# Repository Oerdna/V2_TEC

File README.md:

# V2_TEC
Redesigned PCB for simultaneous Peltier control and surface resistance measurement

------

## Composition
The complex consists of two boards - Signal and Power. The power acts like as a controller of the Peltier element. Signal measures surface resistance and temperature.
In the table, the top line is the signal board. Lower - power. Drawings as part of a work of art.

|  |  |
| ------------------------------------------------------------ | ------------------------------------------------------------ |
|  |  |

More details about the device can be understood from the schematic drawing [here](https://github.com/Oerdna/V2_TEC/blob/main/TEC2/TEC2.pdf). The notes are in Russian.

The controller for the complex is `STM32L432KC Nucleo`.

## Reference Information:
* To control the Peltier element, a `100 kHz PWM` is used.
* `IRS2104` is used to control transistors.
* The measurement of surface resistance is carried out by the `four-probe method`.
* Temperature measurement is carried out by `pt100`.
* There is an additional port for the `I2C` protocol

## 4point_probe

 |  | Four point probe is used to measure resistive properties of semiconductor wafers and thin films [[1](https://www.pveducation.org/pvcdrom/characterisation/four-point-probe-resistivity-measurements)]. |
| ------------------------------------------------------------ | ------------------------------------------------------------ |

In this case are studing the I - V characteristic of an element depending on the temperature of the sample. It is important to understand the I – V characteristic near the metal-insulator phase transition (MIT), which is about 68 degrees Celsius. You must understand that the ultimate goal is to stabilize the temperature to a specific value. More about the TEC control [[2](https://www.maximintegrated.com/en/design/technical-documents/tutorials/1/1757.html)]

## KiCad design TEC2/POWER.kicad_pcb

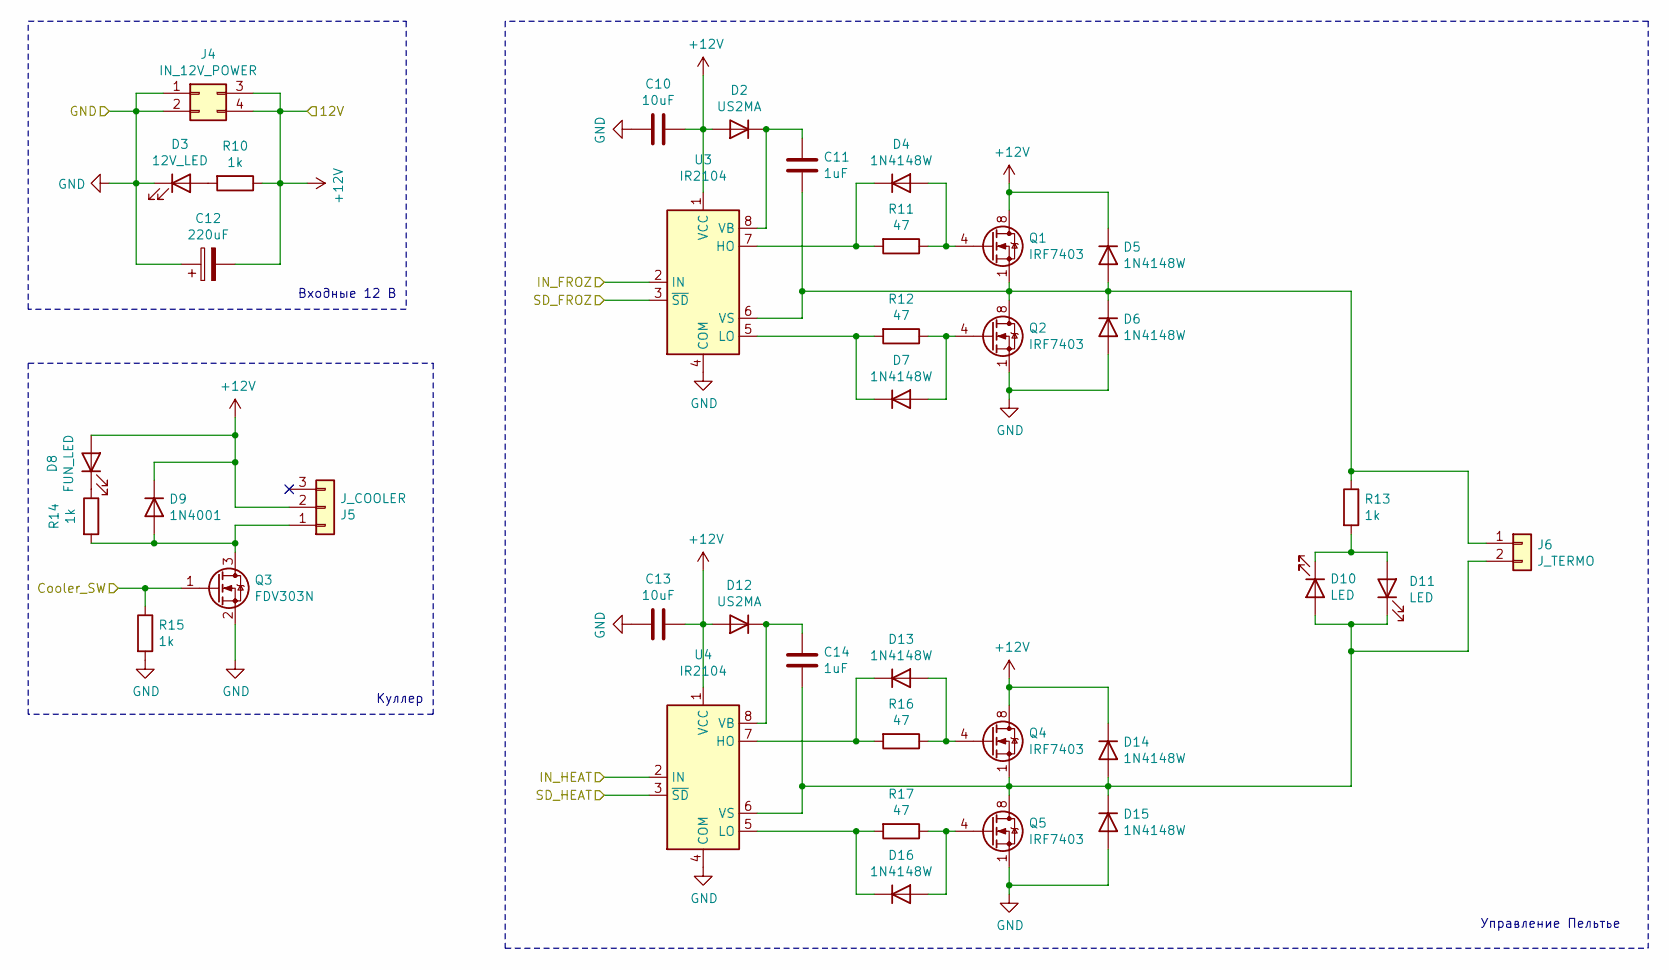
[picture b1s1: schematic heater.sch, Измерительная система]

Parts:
C10, C13: 10uF; C_0805_2012Metric_Pad1.18x1.45mm_HandSolder; JLC 0805
C11, C14: 1uF; C_0805_2012Metric_Pad1.18x1.45mm_HandSolder; JLC 0805
C12: 220uF; CP_Elec_8x10.5
D2, D12: US2MA; D_SMA
D3: 12V_LED; LED_1206_3216Metric_Castellated
D4, D5, D6, D7, D13, D14, D15, D16: 1N4148W; D_SOD-123
D8: FUN_LED; LED_1206_3216Metric_Castellated
D9: 1N4001; D_SMA-SMB_Universal_Handsoldering
D10, D11: LED; LED_0805_2012Metric_Castellated
J4: IN_12V_POWER; Molex_Mini-Fit_Jr_5569-04A2_2x02_P4.20mm_Horizontal
J5: J_COOLER; PinHeader_1x03_P2.54mm_Horizontal
J6: J_TERMO; Amass_XT60PW-M
Q1, Q2, Q4, Q5: IRF7403; SOIC-8_3.9x4.9mm_P1.27mm
Q3: FDV303N; SOT-23
R10, R13, R14, R15: 1k; R_1206_3216Metric_Pad1.30x1.75mm_HandSolder; JLC 1206
R11, R12, R16, R17: 47; R_2512_6332Metric_Pad1.40x3.35mm_HandSolder
U3, U4: IR2104; SOIC-8_3.9x4.9mm_P1.27mm

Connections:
+12V: C10.2, C12.2, C13.2, D2.2 (A), D5.1 (K), D8.2 (A), D9.1 (K), D12.2 (A), D14.1 (K), J4.3, J4.4, J5.2, Q1.5 (D), Q1.6 (D), Q1.7 (D), Q1.8 (D), Q4.5 (D), Q4.6 (D), Q4.7 (D), Q4.8 (D), R10.1, U3.1 (VCC), U4.1 (VCC); also elsewhere on the board
/IN_F: U3.2 (IN); also elsewhere on the board
/IN_H: U4.2 (IN); also elsewhere on the board
/SD_F: U3.3 (~SD); also elsewhere on the board
/SD_H: U4.3 (~SD); also elsewhere on the board
/SW_C: Q3.1 (G), R15.1; also elsewhere on the board
GND: C10.1, C12.1, C13.1, D3.1 (K), D6.2 (A), D15.2 (A), J4.1, J4.2, Q2.1 (S), Q2.2 (S), Q2.3 (S), Q3.2 (S), Q5.1 (S), Q5.2 (S), Q5.3 (S), R15.2, U3.4 (COM), U4.4 (COM); also elsewhere on the board
unnamed: C11.1, D2.1 (K), U3.8 (VB)
unnamed: C11.2, D5.2 (A), D6.1 (K), J6.1, Q1.1 (S), Q1.2 (S), Q1.3 (S), Q2.5 (D), Q2.6 (D), Q2.7 (D), Q2.8 (D), R13.1, U3.6 (VS)
unnamed: C14.1, D12.1 (K), U4.8 (VB)
unnamed: C14.2, D10.2 (A), D11.1 (K), D14.2 (A), D15.1 (K), J6.2, Q4.1 (S), Q4.2 (S), Q4.3 (S), Q5.5 (D), Q5.6 (D), Q5.7 (D), Q5.8 (D), U4.6 (VS)
unnamed: D3.2 (A), R10.2
unnamed: D4.1 (K), R11.2, U3.7 (HO)
unnamed: D4.2 (A), Q1.4 (G), R11.1
unnamed: D7.1 (K), R12.2, U3.5 (LO)
unnamed: D7.2 (A), Q2.4 (G), R12.1
unnamed: D8.1 (K), R14.1
unnamed: D9.2 (A), J5.1, Q3.3 (D), R14.2
unnamed: D10.1 (K), D11.2 (A), R13.2
unnamed: D13.1 (K), R16.2, U4.7 (HO)
unnamed: D13.2 (A), Q4.4 (G), R16.1
unnamed: D16.1 (K), R17.2, U4.5 (LO)
unnamed: D16.2 (A), Q5.4 (G), R17.1

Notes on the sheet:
Куллер
Управление Пельтье
Входные 12 В

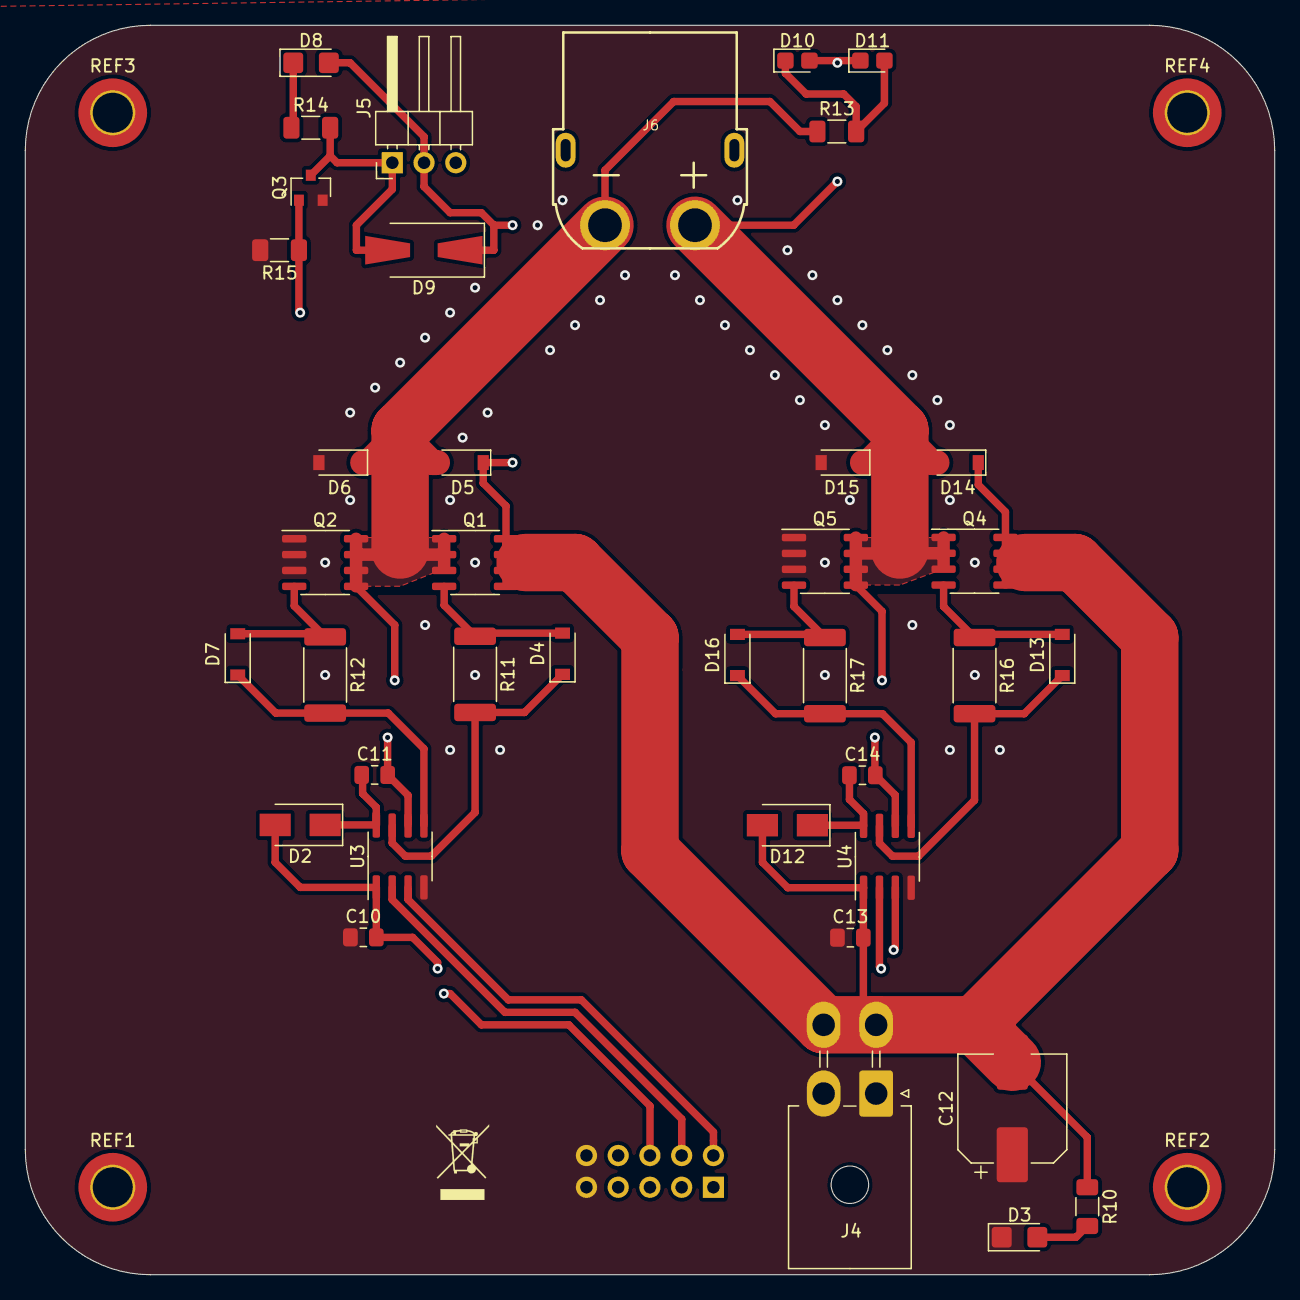
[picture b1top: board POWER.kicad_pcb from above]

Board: 4 copper layers, 100.0 x 100.0 mm, 43 parts (1 on the bottom side), 23 nets.

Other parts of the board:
J2: J_PCB_DOWN; PinHeader_2x05_P2.54mm_Vertical
REF1, REF2, REF3, REF4: MountingHole_3.2mm_M3_ISO14580_Pad_TopOnly

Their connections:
+12V: J2.7, J2.8; also elsewhere on the board
/IN_F: J2.4; also elsewhere on the board
/IN_H: J2.3; also elsewhere on the board
/SD_F: J2.2; also elsewhere on the board
/SD_H: J2.1; also elsewhere on the board
/SW_C: J2.6; also elsewhere on the board
GND: J2.9, J2.10; also elsewhere on the board

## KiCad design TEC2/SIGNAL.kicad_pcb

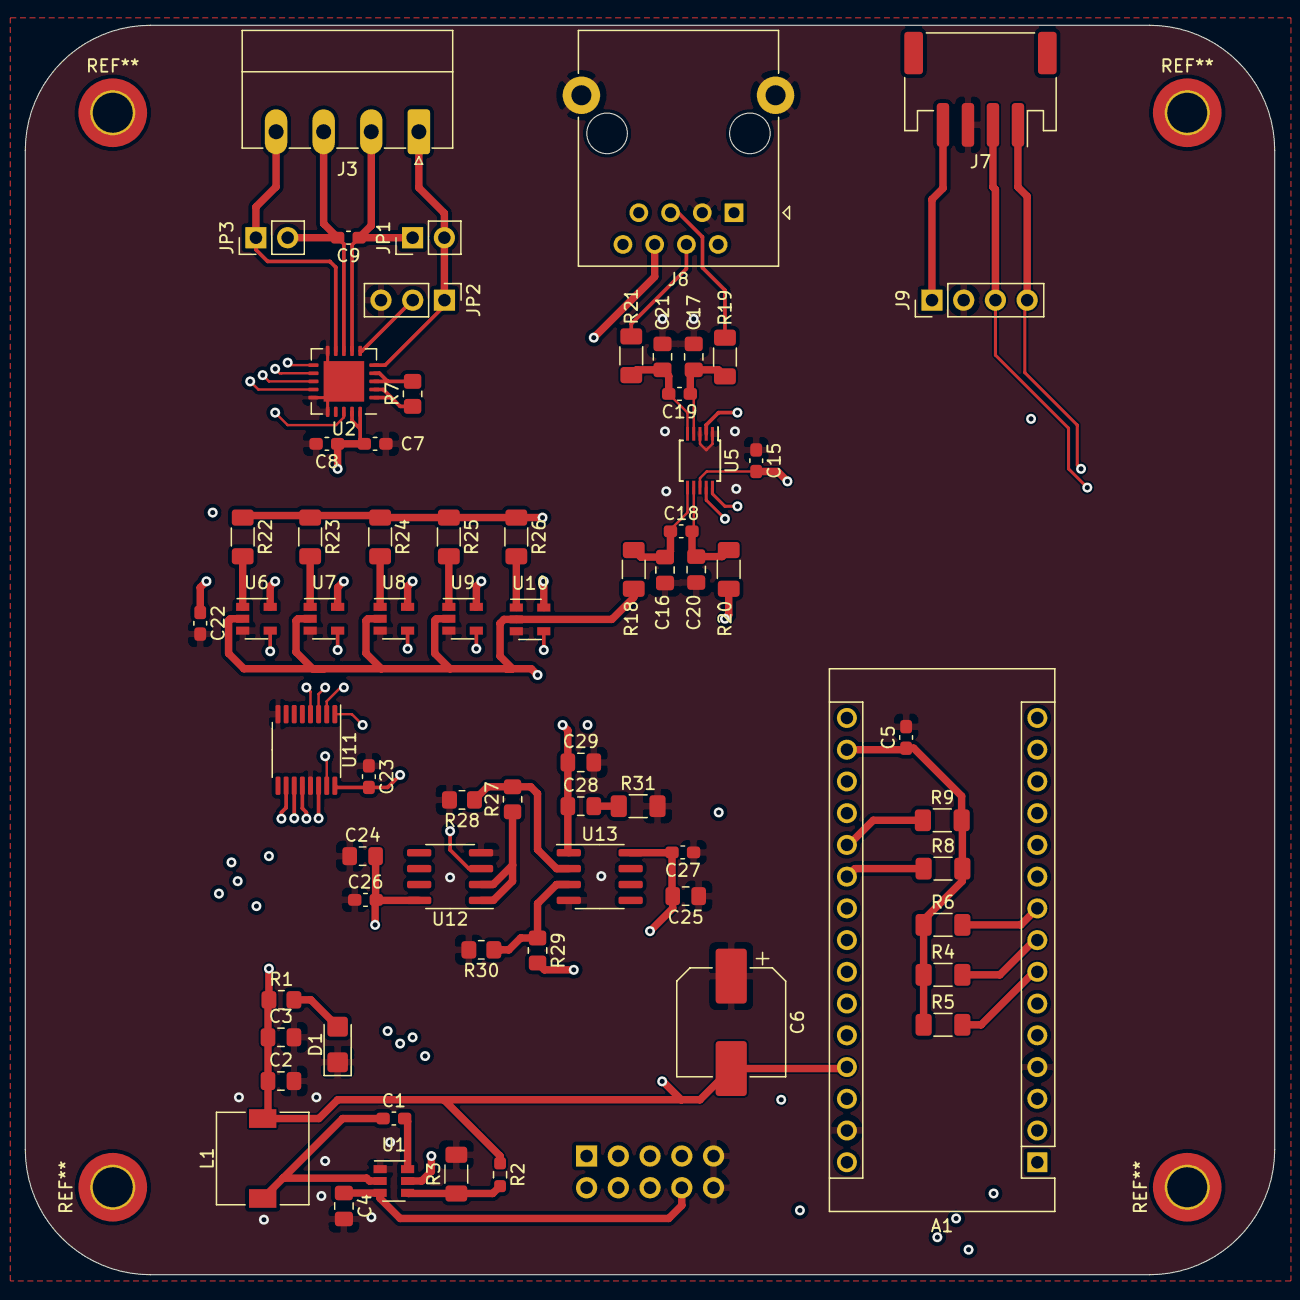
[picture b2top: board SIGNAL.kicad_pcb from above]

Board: 4 copper layers, 100.0 x 100.0 mm, 69 parts (1 on the bottom side), 55 nets.

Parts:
A1: Arduino_Nano_v3.x; Arduino_Nano
C1, C5, C7, C8, C9, C15, C22, C23, C26, C27: 100nF; C_0603_1608Metric_Pad1.08x0.95mm_HandSolder
C2, C3, C4, C24, C25: 10uF; C_0805_2012Metric_Pad1.18x1.45mm_HandSolder
C6: 220uF; CP_Elec_8x10.5
C16, C17, C20, C21, C29: 6nF; C_0805_2012Metric_Pad1.18x1.45mm_HandSolder
C18, C19: 62nF; C_0603_1608Metric_Pad1.08x0.95mm_HandSolder
C28: 470nf; C_0805_2012Metric_Pad1.18x1.45mm_HandSolder
D1: 5V_LED; LED_1206_3216Metric_Castellated
J1: J_PCB_UPPER; PinHeader_2x05_P2.54mm_Vertical
J3: ToPT100; PhoenixContact_MC_1,5_4-G-3.81_1x04_P3.81mm_Horizontal
J7: I2C_Port; JST_PH_S4B-PH-SM4-TB_1x04-1MP_P2.00mm_Horizontal
J8: RJ45_Shielded; RJ45_Ninigi_GE
J9: I2C_dbg; PinHeader_1x04_P2.54mm_Vertical
JP1: SJ2; PinHeader_1x02_P2.54mm_Vertical
JP2: SJ1; PinHeader_1x03_P2.54mm_Vertical
JP3: SJ3; PinHeader_1x02_P2.54mm_Vertical
L1: 4.7uH; L_7.3x7.3_H4.5
R1: 430; R_0805_2012Metric_Pad1.20x1.40mm_HandSolder
R2: 56.2k; R_0603_1608Metric_Pad0.98x0.95mm_HandSolder
R3, R4, R5, R6, R8, R9, R26: 10k; R_1206_3216Metric_Pad1.30x1.75mm_HandSolder
R7: 390; R_0805_2012Metric_Pad1.20x1.40mm_HandSolder
R18, R19, R20, R21, R24, R31: 100; R_1206_3216Metric_Pad1.30x1.75mm_HandSolder
R22: 1; R_1206_3216Metric_Pad1.30x1.75mm_HandSolder
R23: 10; R_1206_3216Metric_Pad1.30x1.75mm_HandSolder
R25: 1k; R_1206_3216Metric_Pad1.30x1.75mm_HandSolder
R27, R30: 20k; R_0805_2012Metric_Pad1.20x1.40mm_HandSolder
R28, R29: 13k; R_0805_2012Metric_Pad1.20x1.40mm_HandSolder
U1: TPS562200; SOT-23-6
U2: MAX31865xTP; TQFN-20-1EP_5x5mm_P0.65mm_EP3.25x3.25mm
U5: ADS1115IDGS; TSSOP-10_3x3mm_P0.5mm
U6, U7, U8, U9, U10: TS5A3166DBVR; SOT-23-5
U11: 74HC595; TSSOP-16_4.4x5mm_P0.65mm
U12: AD8572; SOIC-8_3.9x4.9mm_P1.27mm
U13: AD8606ARZ; SOIC-8_3.9x4.9mm_P1.27mm

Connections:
+3V3: A1.17, C5.1, C7.2, C8.1, C22.1, C23.2, J7.4, J9.1, R4.1, R5.1, R6.1, R8.2, R9.2, U2.19, U2.20, U6.5, U7.5, U8.5, U9.5, U10.5, U11.16
+5V: A1.27, C2.1, C3.1, C6.2, C15.2, C24.2, C25.2, C26.2, C27.2, L1.2, R1.1, R2.1, U5.8, U12.8, U13.8
+12P: C4.1, J1.7, J1.8, U1.3, U1.5
/4PP/AIN_I1: C16.2, C18.1, R18.1, U5.6
/4PP/AIN_I2: C18.2, C20.1, R20.1, U5.7
/4PP/AIN_V1: C17.2, C19.1, R19.1, U5.4
/4PP/AIN_V2: C19.2, C21.1, R21.1, U5.5
/4PP/PROBE1: J8.5, R19.2
/4PP/PROBE2: J8.4, R21.2
/4PP/R1: U6.4, U11.15
/4PP/R1k: U9.4, U11.3
/4PP/R10: U7.4, U11.1
/4PP/R10k: U10.4, U11.4
/4PP/R100: U8.4, U11.2
/4PP/R_sel_high: C28.1, C29.1, R18.2, U6.2, U7.2, U8.2, U9.2, U10.2, U13.1
/4PP/R_sel_low: J8.6, R20.2, R22.1, R23.1, R24.1, R25.1, R26.1, U12.3
/ADS1115_RDY: A1.9, R6.2, U5.2
/CLK_SPI: A1.23, U2.12
/CLK_serial: A1.2, U11.11
/Clear_serial: A1.6, U11.10
/Cooler_SW: A1.16, J1.6
/DAC_out: A1.22, R29.2
/Data_serial: A1.1, U11.14
/IN_FROZ: A1.12, J1.4
/IN_HEAT: A1.13, J1.3
/MISO: A1.24, U2.14
/MOSI: A1.25, U2.11
/SCL_i2c: A1.8, J7.1, J9.4, R4.2, U5.10
/SDA_i2c: A1.7, J7.2, J9.3, R5.2, U5.9
/SD_FROZ: A1.14, J1.2
/SD_HEAT: A1.15, J1.1
/Store_serial: A1.5, U11.12
/TEMP_CS: A1.21, R8.1, U2.13
/TEMP_RDY: A1.20, R9.1, U2.18
GNDD: A1.4, A1.29, C2.2, C3.2, C4.2, C5.2, C6.1, C7.1, C8.2, C15.1, C16.1, C17.1, C20.2, C21.2, C22.2, C23.1, C24.1, C25.1, C26.1, C27.1, C29.2, D1.1, J1.9, J1.10, J7.3, J8.3, J8.SH, J9.2, JP2.3, R3.2, R28.2, R30.2, R31.2, U1.1, U2.10, U2.15, U2.16, U2.21, U5.1, U5.3, U6.3, U7.3, U8.3, U9.3, U10.3, U11.8, U11.13, U12.4, U13.4
unnamed: C1.1, L1.1, U1.2
unnamed: C1.2, U1.6
unnamed: C9.1, J3.2, JP1.1, U2.7
unnamed: C9.2, J3.3, JP3.2, U2.8
unnamed: C28.2, R31.1
unnamed: D1.2, R1.2
unnamed: J3.1, JP1.2, JP2.1, U2.5
unnamed: J3.4, JP3.1, U2.9
unnamed: JP2.2, U2.6
unnamed: R2.2, R3.1, U1.4
unnamed: R7.1, U2.1, U2.2
unnamed: R7.2, U2.3, U2.4
unnamed: R22.2, U6.1
unnamed: R23.2, U7.1
unnamed: R24.2, U8.1
unnamed: R25.2, U9.1
unnamed: R26.2, U10.1
unnamed: R27.1, U12.1, U12.2
unnamed: R27.2, R28.1, U13.2
unnamed: R29.1, R30.1, U13.3

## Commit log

2021-11-07 Add files via upload
    V.1.0.0
